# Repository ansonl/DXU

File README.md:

# DXU - Dual Extrusion Upgrade for Ultimaker Original+ and Ultimaker 2+

## Table of Contents

- ### [Marlin 2 firmware, calibration, and configuration instructions for DXUv2](https://github.com/ansonl/DXU/blob/master/Firmware/README.md) 

- ### [DXUv2 3D printable files](https://github.com/ansonl/DXU/tree/master/AL-DXUv2)

  - DXUv2 reuses the stock Ultimaker printhead metal parts for a more compact and durable printhead.

### Improved/Updated DXU resources are in the `AL-*` folders. 

## DXUv2

1. See [post1](https://community.ultimaker.com/topic/24553-dxu-efficient-dual-extrusion-upgrade-for-um2/?do=findComment&comment=320447) and [post2](https://community.ultimaker.com/topic/24553-dxu-efficient-dual-extrusion-upgrade-for-um2/?do=findComment&comment=323266) for DXUv2 info
1. Make all the parts in `AL-DXUv2/master parts to print/` out of high temperature plastic like SLS Nylon.
1. Make the 3 hotend holder models in `AL-DXUv2/prototyping parts/DXUv2-hotend-holder` out of aluminum. You can machine it out of the existing Ultimaker part or get it SLM printed in aluminum. I did both and the SLM printed part from UnionFab is much more precise. Have the factory use my specification PDF for the threading depths and locations. This is save you a lot of crying and pain trying to thread blind holes yourself.

## Original DXU

1. [Marlin 2 firmware for DXU](https://github.com/ansonl/Marlin-DXU)
2. Dock adapted for UMO+ frame
3. Heater clamps with 1mm thin jaws. The linked Taobao seller sells a quality all metal hotend but the heatsink flanges are only 1mm vs 2mm apart. The seller says he can do a special order of heatsinks with 2mm flange spacing with a minimum order quantity of 50. 
4. Cura profile with calibration and improvements for DXU UMO+ are merged into Cura. 
5. Input Shaping calibration gcode and presets.

## Cura profile notes

I have not had time to update all the downloadable Cura profiles with the [better adaptive start/end gcode](https://ansonliu.com/2024/10/cura-adaptive-dual-extruder-start-gcode/) located in `AL-DXUv2/start-end-gcode`. Please copy and paste them into your Cura printer settings to use them.

### DISCUSSION:
https://community.ultimaker.com/topic/24553-dxu-another-dual-extrusion-upgrade-for-um2/

### CREDITS:

##### DXU:  
Original DXU by yyh1002

DXU variant by benleo888
##### Hardware:  
Lever action is inspired by Ultimaker 3.   
##### Firmware:   
Marlin 2 firmware

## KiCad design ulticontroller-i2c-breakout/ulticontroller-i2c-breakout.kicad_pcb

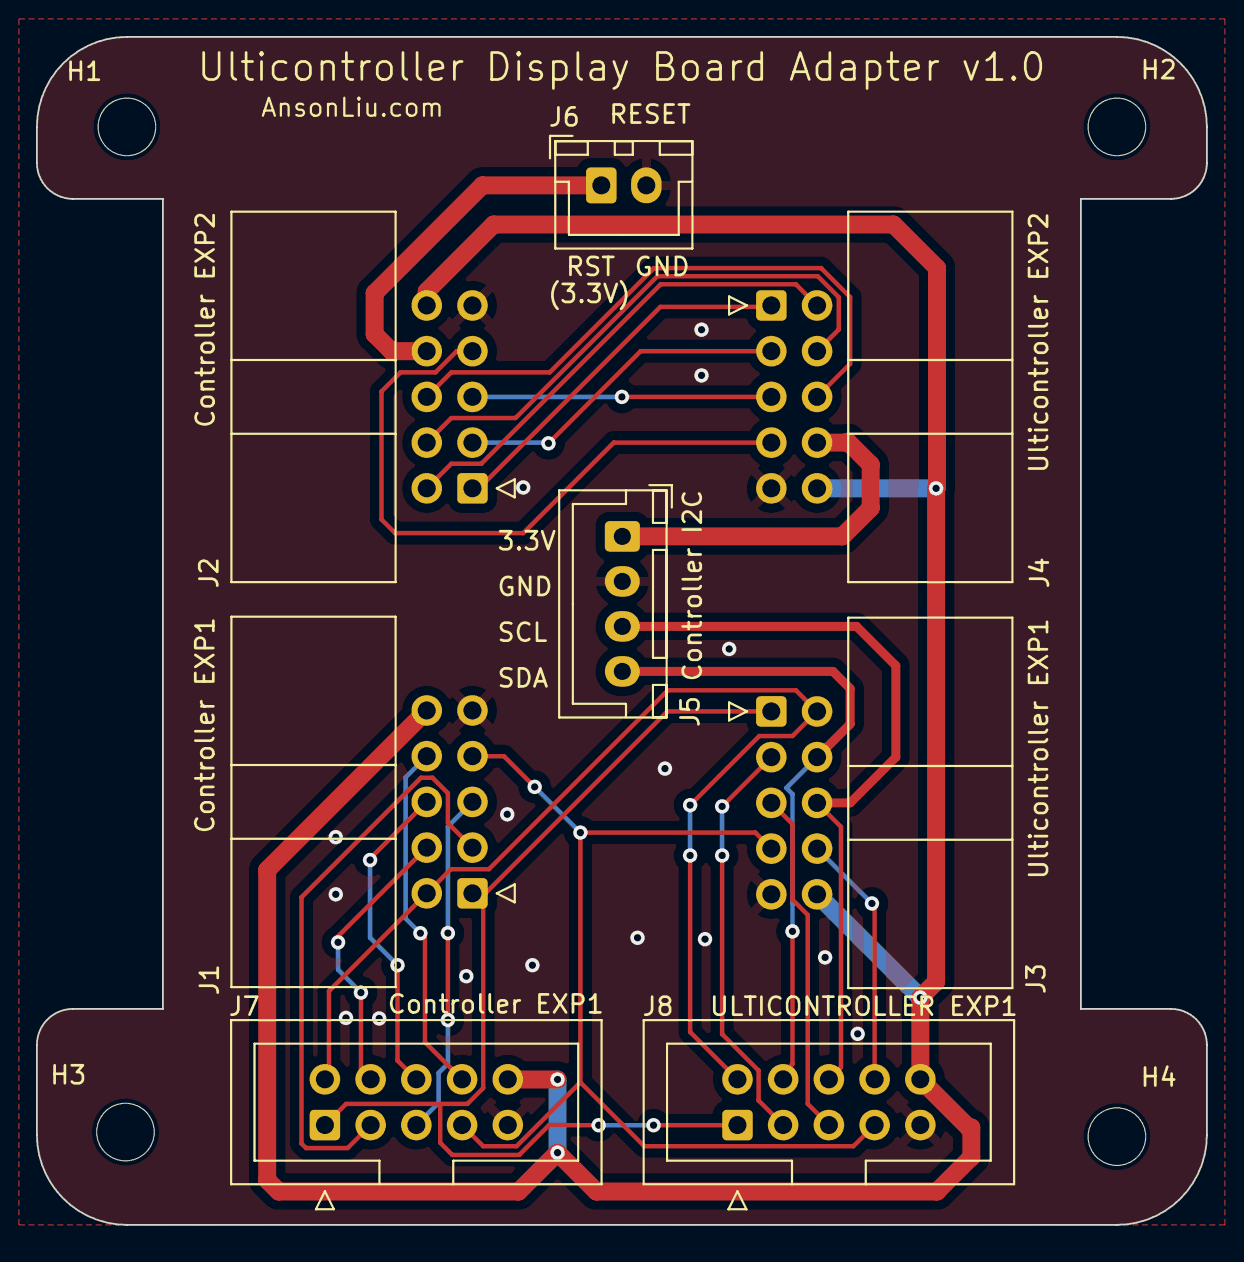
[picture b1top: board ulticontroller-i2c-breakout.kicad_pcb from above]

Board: 2 copper layers, 65.0 x 66.0 mm, 12 parts (0 on the bottom side), 24 nets.

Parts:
H1, H2, H3, H4: MountingHole; MountingHole_3.2mm_M3
J1: Controller EXP1; IDC-Header_2x05_P2.54mm_Horizontal
J2: Controller EXP2; IDC-Header_2x05_P2.54mm_Horizontal
J3: Ulticontroller EXP1; IDC-Header_2x05_P2.54mm_Horizontal
J4: Ulticontroller EXP2; IDC-Header_2x05_P2.54mm_Horizontal
J5: Controller I2C; JST_XH_B4B-XH-A_1x04_P2.50mm_Vertical
J6: RESET; JST_XH_B2B-XH-A_1x02_P2.50mm_Vertical
J7: Controller EXP1; IDC-Header_2x05_P2.54mm_Vertical
J8: ULTICONTROLLER EXP1; IDC-Header_2x05_P2.54mm_Vertical

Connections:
+3.3V: J4.8 (3.3V), J5.1 (+3.3V)
+5V: J1.10 (5V), J2.10 (5V), J3.10 (5V), J4.10 (5V), J7.10, J8.10
BEEP: J1.1 (BEEP), J3.1 (BEEP), J7.1, J8.1
BTN_ENC: J1.2 (BTN_ENC), J3.2 (BTN_ENC), J7.2, J8.2
EXT_PIN4: J3.5 (EXT_PIN4), J8.5
EXT_PIN5: J3.8 (EXT_PIN5), J8.8
EXT_PIN6: J3.3 (EXT_PIN6), J8.3
GND: J1.9 (GND), J2.9 (GND), J3.9 (GND), J4.9 (GND), J5.2 (GND), J6.2, J7.9, J8.9
I2C_N: J3.6 (SCL5), J5.3 (SCL), J8.6
I2C_P: J3.4 (SDA5), J5.4 (SDA), J8.4
LCD_D4: J1.5 (LCD_D4), J7.5
LCD_D5: J1.6 (LCD_D5), J7.6
LCD_D6: J1.7 (LCD_D6), J3.7 (LCD_RST), J7.7, J8.7
LCD_D7: J1.8 (LCD_D7), J7.8
LCD_EN: J1.3 (LCD_EN), J7.3
LCD_RS: J1.4 (LCD_RS), J7.4
unnamed: J2.1 (LCD_MISO), J4.1 (MISO)
unnamed: J2.2 (LCD_SCK), J4.2 (SCK)
unnamed: J2.3 (BTN_EN1), J4.3 (S_E1)
unnamed: J2.4 (LCD_SS), J4.4 (SS)
unnamed: J2.5 (BTN_EN2), J4.5 (S_E2)
unnamed: J2.6 (LCD_MOSI), J4.6 (MOSI)
unnamed: J2.7 (SD_DETECT), J4.7 (SD_CARDDT)
unnamed: J2.8 (RST), J6.1

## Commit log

2022-12-28 initial stable changes
2023-01-08 reorganized and added input shaping calibration
2023-02-28 add DXUv2 design
2023-02-28 rename to DXUv1
2023-02-28 rearrange files for DXUv2
2023-03-20 rename input shaping tower
2023-03-25 DXUv2
2023-03-31 add breakout board
2023-06-17 add DXUv2 files
2023-06-17 add spool holder
2023-06-17 add pictures
2023-07-06 add ESP-EYE mount
2023-07-16 add Cura configs
2023-07-29 Rename start-gcode-single-print.gcode to start-gcode-single-extruder.gcode
2023-07-29 Rename start-gcode.gcode to start-gcode-dual-extruder.gcode
2023-08-07 Update cura default printer settings
2023-12-15 Added extruders for Cura profile and zip file
2023-12-15 add instructions for cura
2024-02-17 Enable relative extrusion
2024-03-23 update start gcode
2024-04-30 add cura5.7 start gcode
2025-04-21 Update README.md with DXUv2 latest notes
